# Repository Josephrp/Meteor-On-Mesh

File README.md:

# Meshtonic

**Meshtonic H4M Companion v2** is a custom carrier board and firmware stack for a [Seeed XIAO ESP32-S3 Plus](https://www.seeedstudio.com/Seeed-Studio-XIAO-ESP32S3-Plus-p-6361.html) that docks to a **HackRF + PortaPack H4M (Mayhem)** and can also run as a **standalone Meshtastic** mesh node.

**Repository:** [github.com/Josephrp/meshtonic](https://github.com/Josephrp/meshtonic) (formerly `Meteor-On-Mesh`)

| Mode | Role |
|------|------|
| **Docked (Mayhem MDK)** | ESP32 is an I2C slave at `0x51` on the PortaPack MDK connector. Exposes GPS, sensors, web UI, and 1–4 LoRa radios to Mayhem; runs the on-device LoRa decoder EPApp. |
| **Standalone (Meshtastic)** | Flash the Meshtastic image instead. Board becomes a LoRa mesh node with GPS, TFT, and muxed sensors. |

The two ESP32 firmwares are **mutually exclusive** — flash one or the other depending on whether you are using the board docked or as a mesh node.

---

## Hardware overview

| Block | Parts |
|-------|--------|
| **MCU** | Seeed XIAO ESP32-S3 Plus (ESP32-S3, 16 MB flash, OPI PSRAM) |
| **LoRa** | Up to **4×** [Wio-SX1262](https://www.seeedstudio.com/) shields — shared SPI, per-radio CS on native GPIO, BUSY/DIO1/RST via **MCP23017** `@ 0x20` |
| **Sensors** | **TCA9548A** `@ 0x70` mux: BMM150, BMP280, SHT3x, BMI160; **AS5600** on the main I2C bus |
| **GPS** | NEO-6M (UART1) |
| **Display / storage** | ILI9341 240×320 SPI TFT, microSD |
| **Host link** | PortaPack H4M / MDK-compatible connector (I2C slave + power) |
| **Power** | USB / solar → **CN3170** LiPo charge → **TPS63020** 3.3 V buck-boost |

Canonical pin map (silicon GPIO numbers for the XIAO Plus — `Dn ≠ GPIOn` above D5):

- Shared SPI: MOSI / MISO / SCK = GPIO 38 / 39 / 40  
- I2C: SDA / SCL = GPIO 5 / 6  
- WIO1–4 CS: GPIO 3 / 4 / 10 / 13  
- MCP INTA: GPIO 44 · WIO1 DIO1: GPIO 12  
- Full table: [`firmwares/pin_mapping.cpp`](firmwares/pin_mapping.cpp) and the variant [`PIN_AUDIT.md`](firmwares/meshtastic/variants/esp32s3/diy/meshtonic_h4m_wio1/PIN_AUDIT.md)

<p align="center">
  
  <br />

</p>

Architecture notes for the docked LoRa path (MCP ISR → radio manager → decoder → web / PortaPack) live in [`static/diagrams.md`](static/diagrams.md).

### Enclosure

3D-printable case STLs (65 × 140 mm footprint):

- [`case/enclosure_base_65x140x32.stl`](case/enclosure_base_65x140x32.stl)
- [`case/enclosure_lid_65x140.stl`](case/enclosure_lid_65x140.stl)

---

## Software stack

| Tree | Upstream | Meshtonic role |
|------|----------|----------------|
| [`firmwares/meshtastic/`](firmwares/meshtastic/) | [Meshtastic firmware](https://github.com/meshtastic/firmware) (GPL-3.0) | Custom board env `meshtonic-h4m-wio1` — WIO1-first standalone mesh |
| [`firmwares/mayhem-mdk/`](firmwares/mayhem-mdk/) | [ESP32-Portapack / Mayhem MDK](https://github.com/htotoo/ESP32-Portapack) (HTL) | Docked companion: `HW_VARIANT_MESHTONIC_H4M`, MCP + TCA drivers, multi-slot SX1262 manager, LoRa decoder EPApp, optional host LWD bridge |
| [`firmwares/mayhem-firmware/`](firmwares/mayhem-firmware/) | [PortaPack Mayhem](https://github.com/portapack-mayhem/mayhem-firmware) (GPL-3.0) | Vendored Mayhem tree + PortaPack UI app under `firmware/standalone/meshtonic_lora/` |

Shared first-party pin constants: [`firmwares/pin_mapping.cpp`](firmwares/pin_mapping.cpp).

### Docked LoRa decoder (MDK)

When Mayhem MDK is flashed with the Meshtonic H4M profile:

1. ESP32 auto-runs the LoRa Decoder EPApp.
2. Up to four Wio-SX1262 modules listen in parallel (narrowband).
3. Optional HackRF wideband path: PortaPack sends short IQ bursts over I2C (`0xA012`); ESP DSP + decode run on-device.
4. Status and packets paint on the PortaPack LCD (Apps over I2C) and/or the ESP web UI.

Protocol and backend IDs: [`firmwares/mayhem-mdk/docs/PORTAPACK_LORADEC.md`](firmwares/mayhem-mdk/docs/PORTAPACK_LORADEC.md).

```mermaid
flowchart TD
  Board["Meshtonic H4M (1-4 Wio SX1262)"] -->|MCP23017 + shared SPI| Radios["LoraRadio slots"]
  Radios --> EPApp["EPAppLoraDecoder"]
  EPApp --> Decode["Decode layer"]
  Decode --> Packets["LoraPacket"]
  Packets --> Web["Web / WS"]
  Packets --> PP["PortaPack I2C @ 0x51"]
  HostLWD["Host LWD optional"] -.-> Packets
```

---

## Repository map

```
meshtonic/
├── pcb/                 # KiCad project meshtonic_h4m_v2 (schematics, PCB, BOM, DFM)
├── firmwares/
│   ├── meshtastic/      # Meshtastic + meshtonic_h4m_wio1 variant
│   ├── mayhem-mdk/      # ESP32 Mayhem MDK + Meshtonic H4M profile
│   ├── mayhem-firmware/ # PortaPack Mayhem (+ meshtonic_lora PP app)
│   └── pin_mapping.cpp  # Canonical H4M v2 GPIO / MCP map
├── case/                # Enclosure STLs
├── static/              # Photos, pinout / architecture diagrams, demos
└── README.md
```

Local-only (gitignored) folders such as `refs/` and `backups/` may hold design plans and PCB snapshots on a developer machine; they are not part of the tracked tree.

---

## Getting started

### Prerequisites

| Firmware | Toolchain |
|----------|-----------|
| Meshtastic | [PlatformIO](https://platformio.org/) (CLI or IDE) |
| Mayhem MDK | [ESP-IDF](https://docs.espressif.com/projects/esp-idf/en/latest/esp32s3/) targeting `esp32s3`, or the Docker builders under `firmwares/mayhem-mdk/docker/` |
| PortaPack app | Mayhem firmware build environment (see upstream Mayhem docs) |

Hardware bring-up checklist (I2C scan + radio):

- MCP23017 `@ 0x20`, TCA9548A `@ 0x70`, AS5600 `@ 0x36`
- SX1262 init on populated WIO slot(s)
- GPS NMEA on UART1
- ILI9341 bring-up (standalone Meshtastic)
- LoRa TX/RX with a second Meshtastic node (standalone)

### Flash Meshtastic (standalone)

```bash
cd firmwares/meshtastic
pio run -e meshtonic-h4m-wio1
pio run -e meshtonic-h4m-wio1 -t upload
pio device monitor -b 115200
```

- Board definition: [`boards/meshtonic_h4m_wio1.json`](firmwares/meshtastic/boards/meshtonic_h4m_wio1.json)
- Variant docs: [`variants/esp32s3/diy/meshtonic_h4m_wio1/`](firmwares/meshtastic/variants/esp32s3/diy/meshtonic_h4m_wio1/)
- Upload uses esptool @ 921600 with 1200 bps touch / wait-for-port (16 MB flash)
- Current Meshtastic port is **WIO1-first** (one radio). Multi-radio listening is implemented on the MDK side.

### Flash Mayhem MDK (docked companion)

```bash
cd firmwares/mayhem-mdk/Source
idf.py set-target esp32s3
# Select Meshtonic H4M pins: HW_VARIANT_MESHTONIC_H4M in code,
# and/or choose "Meshtonic H4M" in the web pin-config UI after first boot
idf.py build
idf.py -p <PORT> flash monitor
```

Docker alternative:

```bash
cd firmwares/mayhem-mdk/docker
# see build.ps1 / build-in-container.sh / docker-compose.yml
```

Pin preset for Meshtonic H4M: GPS RX = GPIO 7, shared I2C master+slave on GPIO 5/6 (`HW_VARIANT_MESHTONIC_H4M` in [`pinconfig.h`](firmwares/mayhem-mdk/Source/main/pinconfig.h)).

Optional host-side LoRa wideband decoder / bridge tooling: [`firmwares/mayhem-mdk/lora-wideband-decoder/`](firmwares/mayhem-mdk/lora-wideband-decoder/).

### PortaPack “Meshtonic LoRa” app

PortaPack-side UI that talks to the ESP over Apps-over-I2C lives in:

- [`firmwares/mayhem-firmware/firmware/standalone/meshtonic_lora/`](firmwares/mayhem-firmware/firmware/standalone/meshtonic_lora/)
- Reference / example: [`firmwares/mayhem-mdk/Source/extapps/meshtonic_lora_ui_example.cpp`](firmwares/mayhem-mdk/Source/extapps/meshtonic_lora_ui_example.cpp)

Build and install that app with your usual Mayhem standalone-app workflow, then launch it from the PortaPack App Manager (or rely on Meshtonic H4M auto-start of the ESP decoder).

---

## PCB and manufacturing

KiCad 8 project: **`pcb/meshtonic_h4m_v2`**

| Sheet | Contents |
|-------|----------|
| `meshtonic_h4m_v2.kicad_sch` | Root |
| `Power` | CN3170 charge, TPS63020 3.3 V, battery / solar |
| `Xiao_Core` | XIAO ESP32-S3 Plus |
| `LoRa` | WIO1–4 sockets, MCP23017 radio GPIO |
| `Sensors` | TCA9548A + environmental / IMU / mag |
| `Periferals` | TFT, microSD, GPS, Grove, misc |
| `H4M_Connector` / `MDK_Interface` | PortaPack dock |
| `Breakout_GPIO` | Expansion |

Also: `meshtonic_i2c-hub.kicad_*` for the I2C hub side project.

### BOM / fab

| Artifact | Purpose |
|----------|---------|
| [`pcb/meshtonic_h4m_v2.csv`](pcb/meshtonic_h4m_v2.csv) | Seeed Fusion–oriented PCBA BOM |
| [`pcb/meshtonic_h4m_v2_excluded_from_pcba.csv`](pcb/meshtonic_h4m_v2_excluded_from_pcba.csv) | Hand-fit / DNP (WIO sockets, display, test points, …) |
| [`pcb/_gen_seeed_bom.py`](pcb/_gen_seeed_bom.py) | Regenerates the Seeed BOM + exclusion list |
| [`pcb/dfm/`](pcb/dfm/) | Gerbers, drills, fab zip |

**Hand-fit after PCBA:** Wio-SX1262 modules (and their hybrid SMD+TH landings), display module, and any DNP connectors listed in the exclusion CSV.

Regenerate the Fusion BOM:

```bash
python pcb/_gen_seeed_bom.py
```

---

## Status

This is an active hardware + firmware bring-up project.

- PCB: Meshtonic H4M Companion **v2** (iterating layout / DFM)
- Meshtastic: custom `meshtonic-h4m-wio1` env — single-radio focus
- Mayhem MDK: Meshtonic H4M board profile, multi-radio LoRa decoder path in development
- PortaPack UI app and host LWD bridge: present; expect ongoing protocol/UI work

Demo media: [`static/`](static/) (photos + short videos).

---

## Licenses

This is a **multi-license** monorepo. The root [`LICENSE`](LICENSE) is the index; full texts live under [`LICENSES/`](LICENSES/).

| Component | License |
|-----------|---------|
| `pcb/`, `case/`, `firmwares/pin_mapping.cpp` | [CERN-OHL-P-2.0](LICENSES/CERN-OHL-P-2.0.txt) |
| `README.md`, `static/` | [CC-BY-4.0](LICENSES/CC-BY-4.0.txt) |
| `firmwares/meshtastic/` | [GPL-3.0](firmwares/meshtastic/LICENSE) |
| `firmwares/mayhem-firmware/` | GPL-3.0 (see tree) |
| `firmwares/mayhem-mdk/` | Custom **HTL** — attribution, contribute improvements back, **no commercial use** ([`LICENSE`](firmwares/mayhem-mdk/LICENSE)) |
| `firmwares/mayhem-mdk/lora-wideband-decoder/` | See that subtree’s `LICENSE` |
| `pcb/libs/` | Upstream library licenses (unchanged) |

Meshtonic board support added inside a firmware tree follows that tree’s license unless a file says otherwise. Upstream copyrights remain with their respective authors.

---

## Links

- [This repository](https://github.com/Josephrp/meshtonic)
- [Meshtastic](https://meshtastic.org) · [firmware](https://github.com/meshtastic/firmware)
- [PortaPack Mayhem](https://github.com/portapack-mayhem/mayhem-firmware)
- [ESP32-Portapack / Mayhem MDK](https://github.com/htotoo/ESP32-Portapack) · [wiki](https://github.com/htotoo/ESP32-Portapack/wiki)
- [Seeed XIAO ESP32-S3 Plus](https://www.seeedstudio.com/Seeed-Studio-XIAO-ESP32S3-Plus-p-6361.html)
- In-repo diagrams: [`static/diagrams.md`](static/diagrams.md) · LoRa over I2C: [`docs/PORTAPACK_LORADEC.md`](firmwares/mayhem-mdk/docs/PORTAPACK_LORADEC.md)

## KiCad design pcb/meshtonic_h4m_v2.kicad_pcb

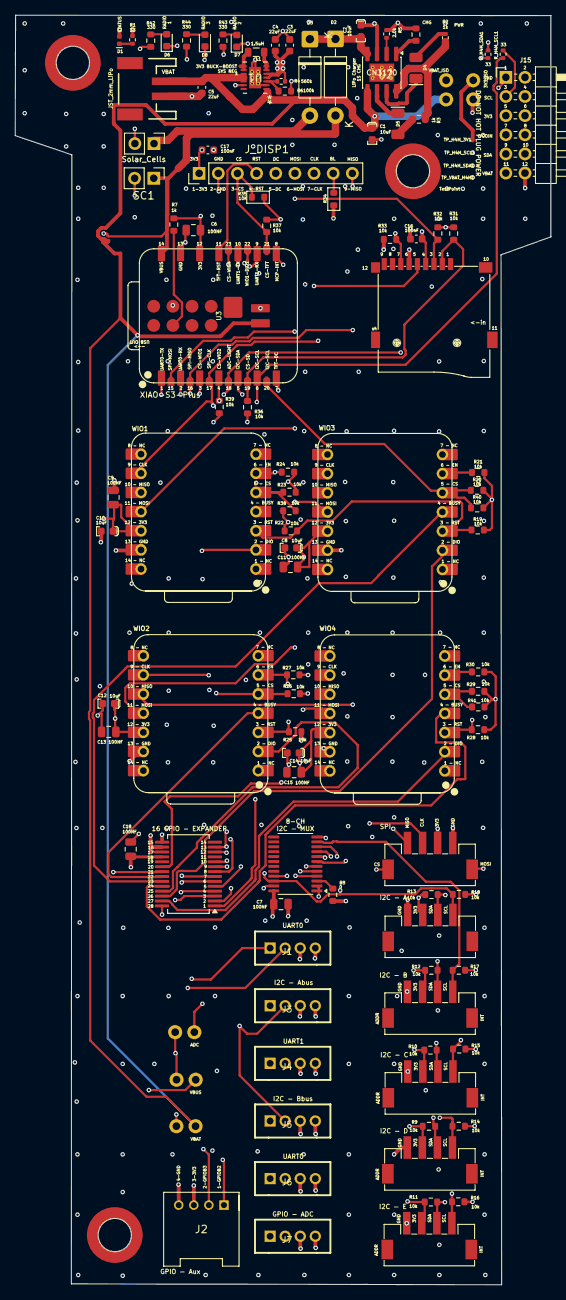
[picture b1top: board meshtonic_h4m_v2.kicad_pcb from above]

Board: 6 copper layers, 71.1 x 168.4 mm, 115 parts (0 on the bottom side), 70 nets.

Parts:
C1, C2, C8, C10, C12, C14: 10uF; C_0603_1608Metric_Polar
C3, C4, C5: 22uF; C_0603_1608Metric
C6, C7, C9, C11, C13, C15, C18: CERAMIC-100NF-50V-10%-X7R_0805_; C_0805_2012Metric
C16, C17: 100nF; C_0603_1608Metric
D1: Red; LED_0402_1005Metric_Red
D2, D3: 1N5819; D_DO-41_SOD81_P10.16mm_Horizontal
D4, D5: Green; LED_1206_3216Metric_Green
D6, D7, D8: LED-SMD-RED-DIFFUSED_0603_; LED_0603_1608Metric
J1, J3, J4, J5, J6, J7: GROVE-CONNECTOR-DIP_4P-2.0_; GROVE-HW4-2.0
J2: GROVE-CONNECTOR-DIP-90D_4P-2.0_; GROVE-HW4-2.0-90D
J8: GROVE-CONNECTOR-SMD_4+2P-2.0_; GROVE-HW4-SMD-2.0
J9, J10, J11: Conn_01x02; 1x02_P2.54mm
J12: JST_2mm_LiPo; JST_1x02_P2.0mm_Horizontal_SMD
J13: Screw_Terminal_01x02; PinHeader_1x02_P2.54mm_Vertical
J14: Micro_SD_Card_passive_clk; MICRO-SD9+4P-SMD-16.1X14.5X1.85MM
J15: H4M_2x6_MDK; PinHeader_2x06_P2.54mm_Horizontal
JP_H4M_3V1: 3V3_ISO; 1x02_P2.54mm
JP_VBAT_H4M1: VBAT_ISO; 1x02_P2.54mm
J_AS1: AS5600_LANDING; GROVE-HW4-SMD-2.0
J_BMI1: BMI160_LANDING; GROVE-HW4-SMD-2.0
J_BMM1: BMM150_LANDING; GROVE-HW4-SMD-2.0
J_BMP1: BMP280_LANDING; GROVE-HW4-SMD-2.0
J_DISP1: DISP_SPI_9P; PinHeader_1x09_P2.54mm_Vertical
J_SHT1: SHT31_LANDING; GROVE-HW4-SMD-2.0
J_WIO1, J_WIO2, J_WIO3, J_WIO4: WioSX1262_Shield_Socket; XIAO-ESP32-S3-DIP
L1: 1.5uH; 0805
R1: 33; R_0402_1005Metric
R2: 1k; R_0402_1005Metric
R3, R7: 1k; R_0603_1608Metric
R4: 560k; R_0402_1005Metric
R5: 2.0k; R_0402_1005Metric
R6: 100k; R_0603_1608Metric
R8, R34: 0; R_0603_1608Metric
R9, R10, R11, R12, R13, R14, R15, R16, R17, R18, R19, R20, R21, R22, R23, R24, R25, R26, R27, R28, R29, R30, R31, R32, R33, R35, R36, R37, R38, R39, R40, R41, R45: 10k; R_0603_1608Metric
R42, R43, R44: 330; R_0603_1608Metric
R_H4M_SCL1, R_H4M_SDA1: 33; R_0402_1005Metric
SC1: Solar_Cells; PinHeader_1x02_P2.54mm_Vertical
ST1, ST2, ST3: Standoff; Standoff_Reflow-M3.0
TP1: TestPoint; TestPoint-0.5mm
TP_H4M_3V1, TP_H4M_SCL1, TP_H4M_SDA1: 0.5mm; TestPoint-0.5mm
TP_VBAT_H4M1: 0.5mm; TestPoint-0.5mm
U1: TPS63020DSJR; DSJ14_2P85X1P58
U2: CN3170; SOIC-8-1EP_3.9x4.9mm_P1.27mm_EP2.41x3.3mm_ThermalVias
U3: XIAO-S3-Plus; XIAO-ESP32-S3-Plus-SMD
U4: TCA9548APWR; TSSOP-24_4.4x7.8mm_P0.65mm
U5: MCP23017x-x-SS; SSOP-28_5.3x10.2mm_P0.65mm

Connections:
3V3: C3.1, C4.1, C6.2, C7.1, C8.1, C9.1, C10.1, C11.1, C12.1, C13.1, C14.1, C15.1, C16.1, C17.2, C18.2, D1.2 (A), D6.1 (+), D7.1 (+), D8.1 (+), J1.3, J2.3, J3.3, J4.3, J5.3, J6.3, J7.3, J8.2, J14.4 (VDD), JP_H4M_3V1.2, J_AS1.3, J_BMI1.3, J_BMM1.3, J_BMP1.3, J_DISP1.1 (VCC), J_SHT1.3, J_WIO1.12, J_WIO2.12, J_WIO3.12, J_WIO4.12, R4.1, R7.2, R8.1, R9.1, R10.1, R11.1, R12.1, R13.1, R14.1, R15.1, R16.1, R17.1, R18.1, R19.2, R20.2, R21.2, R22.2, R23.2, R24.2, R25.2, R26.2, R27.2, R28.2, R29.2, R30.2, R31.2, R32.2, R33.2, R34.2, R35.2, R36.2, R37.2, R38.2, R39.2, R40.2, R41.2, U1.4 (VOUT), U1.5 (VOUT), U3.12 (3V3_OUT), U4.24 (VCC), U5.9 (V_{DD}), U5.18 (~RESET)
/Periferals/LED WIO 1: R42.1, U5.6 (GPB5)
/Periferals/LED WIO 2: R43.1, U5.7 (GPB6)
/Periferals/LED WIO 3: R44.1, U5.8 (GPB7)
/Power/VIN_CHG: C2.2, D2.1 (K), D3.1 (K), U2.4 (VIN)
ADC_LIGHT: J7.2, J11.1, TP1.1 (1_1), U3.18 (D14)
CS_GROVE: J8.6, U5.2 (GPB1)
CS_SD: J14.2 (DAT3/CD), R31.1, R36.1, U3.19 (D15)
CS_TFT: J_DISP1.3 (CS), R35.1, R37.1, U3.21 (D19)
CS_WIO1: J_WIO1.5, R23.1, R38.1, U3.3 (D2)
CS_WIO2: J_WIO2.5, R26.1, R39.1, U3.4 (D3)
CS_WIO3: J_WIO3.5, R20.1, R40.1, U3.20 (D16)
CS_WIO4: J_WIO4.5, R29.1, R41.1, U3.23 (D17)
GND: C1.2, C2.1, C3.2, C4.2, C5.1, C6.1, C7.2, C8.2, C9.2, C10.2, C11.2, C12.2, C13.2, C14.2, C15.2, C16.2, C17.1, C18.1, J1.4, J2.4, J3.4, J4.4, J5.4, J6.4, J7.4, J8.1, J9.2, J10.2, J11.2, J12.1 (-), J13.2, J14.6 (VSS), J15.1, J15.12, J_AS1.4, J_BMI1.4, J_BMM1.4, J_BMP1.4, J_DISP1.2 (GND), J_SHT1.4, J_WIO1.13, J_WIO2.13, J_WIO3.13, J_WIO4.13, R1.2, R5.1, R6.1, R45.2, SC1.2 (-), U1.2 (GND), U1.13 (PS/SYNC), U1.15 (EPAD), U2.3 (GND), U2.9 (GND), U3.13 (GND), U3.27 (GND), U3.33 (GND), U4.1 (A0), U4.2 (A1), U4.12 (GND), U4.21 (A2), U5.10 (V_{SS}), U5.15 (A0), U5.16 (A1), U5.17 (A2)
H4M_3V3: J15.5, J15.8, JP_H4M_3V1.1, TP_H4M_3V1.1 (1_1)
H4M_SCL: J15.3, J15.10, R_H4M_SCL1.1, TP_H4M_SCL1.1 (1_1)
H4M_SDA: J15.4, J15.9, R_H4M_SDA1.1, TP_H4M_SDA1.1 (1_1)
I2C_SCL: J3.1, J5.1, J_AS1.1, R18.2, R_H4M_SCL1.2, U3.6 (D5), U4.22 (SCL), U5.12 (SCK)
I2C_SDA: J3.2, J5.2, J_AS1.2, R13.2, R_H4M_SDA1.2, U3.5 (D4), U4.23 (SDA), U5.13 (SDA)
LORA_RST: J_WIO1.3, J_WIO2.3, J_WIO3.3, J_WIO4.3, R19.1, R22.1, R25.1, R28.1, U5.5 (GPB4)
MCP_GPA7: J7.1, U5.28 (GPA7)
MCP_GPB2: J2.1, U5.3 (GPB2)
MCP_GPB3: J2.2, U5.4 (GPB3)
MCP_INT: U3.8 (D7), U5.20 (INTA)
unnamed: D1.1 (K), R1.1
unnamed: D4.2 (A), R2.2
unnamed: D4.1 (K), U2.7 (~CHRG)
unnamed: D5.2 (A), R3.2
unnamed: D5.1 (K), U2.6 (~DONE)
unnamed: D6.2 (-), R42.2
unnamed: D7.2 (-), R43.2
unnamed: D8.2 (-), R44.2
unnamed: L1.1, U1.6 (L2), U1.7 (L2)
unnamed: L1.2, U1.8 (L1), U1.9 (L1)
unnamed: R4.2, R6.2, U1.3 (FB)
unnamed: R5.2, U2.2 (ISET)
unnamed: R45.1, U2.1 (TEMP)
unnamed: R7.1, U3.26 (EN)
unnamed: R8.2, U4.3 (~RESET)
SENS0_SCL: J_BMM1.1, R14.2, U4.5 (SC0)
SENS0_SDA: J_BMM1.2, R9.2, U4.4 (SD0)
SENS1_SCL: J_BMP1.1, R15.2, U4.7 (SC1)
SENS1_SDA: J_BMP1.2, R10.2, U4.6 (SD1)
SENS2_SCL: J_SHT1.1, R16.2, U4.9 (SC2)
SENS2_SDA: J_SHT1.2, R11.2, U4.8 (SD2)
SENS3_SCL: J_BMI1.1, R17.2, U4.11 (SC3)
SENS3_SDA: J_BMI1.2, R12.2, U4.10 (SD3)
SPI_CLK: J8.3, J14.5 (CLK), J_DISP1.7 (SCK), J_WIO1.9, J_WIO2.9, J_WIO3.9, J_WIO4.9, U3.17 (D13)
SPI_MISO: J8.4, J14.7 (DAT0), J_DISP1.9 (MISO), J_WIO1.10, J_WIO2.10, J_WIO3.10, J_WIO4.10, R33.1, U3.16 (D12)
SPI_MOSI: J8.5, J14.3 (CMD), J_DISP1.6 (MOSI), J_WIO1.11, J_WIO2.11, J_WIO3.11, J_WIO4.11, R32.1, U3.15 (D11)
TFT_BL: J_DISP1.8 (LED), R34.1
TFT_DC: J_DISP1.5 (D/C), U3.7 (D6)
TFT_RST: J_DISP1.4 (RESET), U3.11 (D10)
UART0_RX: J1.1, J6.1, U3.2 (D1)
UART0_TX: J1.2, J6.2, U3.1 (D0)
UART1_RX: J4.1, U3.9 (D8)
UART1_TX: J4.2, U3.10 (D9)
VBAT: C1.1, C5.2, J9.1, J12.2 (+), JP_VBAT_H4M1.2, R2.1, R3.1, U1.1 (VINA), U1.10 (VIN), U1.11 (VIN), U1.12 (EN), U2.5 (BAT), U2.8 (FB), U3.32 (VBAT)
VBAT_H4M: J15.2, J15.11, JP_VBAT_H4M1.1, TP_VBAT_H4M1.1 (1_1)
VBUS: D2.2 (A), D3.2 (A), J10.1, J13.1, SC1.1 (+), U3.14 (VBUS)
VCOIN_H4M: J15.6, J15.7
WIO1_BUSY: J_WIO1.4, U5.21 (GPA0)
WIO1_DIO1: J_WIO1.2, U3.22 (D18)
WIO2_BUSY: J_WIO2.4, U5.22 (GPA1)
WIO2_DIO1: J_WIO2.2, U5.25 (GPA4)
WIO3_BUSY: J_WIO3.4, U5.23 (GPA2)
WIO3_DIO1: J_WIO3.2, U5.26 (GPA5)
WIO4_BUSY: J_WIO4.4, U5.24 (GPA3)
WIO4_DIO1: J_WIO4.2, U5.27 (GPA6)
WIO_RF_SW_EN: J_WIO1.6, J_WIO2.6, J_WIO3.6, J_WIO4.6, R21.1, R24.1, R27.1, R30.1, U5.1 (GPB0)

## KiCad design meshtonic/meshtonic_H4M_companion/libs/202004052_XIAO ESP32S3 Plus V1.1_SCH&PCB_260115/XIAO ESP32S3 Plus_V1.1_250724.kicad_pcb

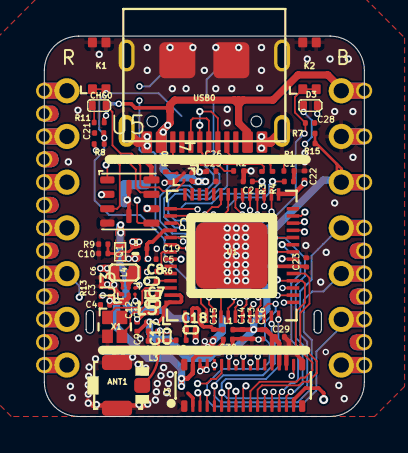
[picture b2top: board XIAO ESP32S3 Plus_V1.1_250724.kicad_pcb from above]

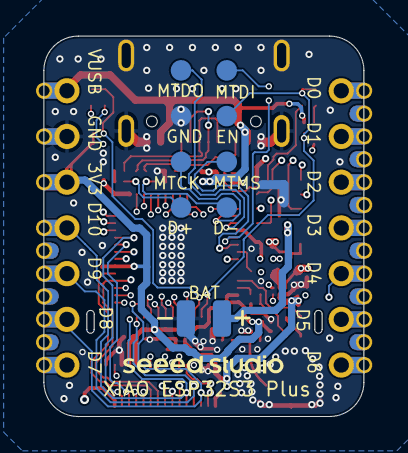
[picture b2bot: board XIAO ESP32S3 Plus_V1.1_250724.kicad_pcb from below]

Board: 6 copper layers, 17.8 x 21.1 mm, 70 parts (10 on the bottom side), 62 nets.

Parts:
ANT1: U.FL-R-SMT-1; U-FL3P-SMD-2.6X2.6X1.0MM
BAT0: VBAT; TP-80X40MIL
C1, C2, C20: DNP; C0201
C3, C9, C13, C16: 2.2uF; C0201
C4, C5, C6: 4.7uF; C0201
C7, C8: 12pF; C0201
C10, C21, C25, C26: 1uF; C0201
C11, C14, C15, C19, C22, C23, C29, C30: 100nF; C0201
C12: 10nF; C0201
C17: 1.2pF; C0201
C18: 1.8pF; C0201
C28: 10pF; C0201
CHG0: RED; LED-0402
D2: LMBR4010BST5G; DFN1006-2L
D3: Yellow; LED-0402
GND0: GND; TP-80X40MIL
J3: 30pin; BTB30-0.4-7.52X2.97X1.14
K1, K2: SKTAAAE010/311021459; SW4-SMD-2.8-2.6X1.6X0.53MM
L1: 2nH; L0201
L2: 3.3nH; L0201
L3: DNP; L0201
L4: 470nH; L0603
L5: 24nH; L0201
Q1: PMOS_1.00.60.35MM; PMOS_1.0*0.6*0.35MM
R1, R2: 5.1K; R0201
R3, R4: 22R; R0201
R6: 499R; R0201
R7, R8, R11: 10K; R0201
R9: 100K; C0201
R10: 220K; R0201
R13: 249K; R0201
R15: 1.5K; R0201
TP1, TP2, TP3, TP4, TP5, TP6, TP7, TP8: TEST-POINT'4545'; TP-D45MIL
U1: MCU-ESP32-S3; QFN56G-0.4-7X7MM
U2: XIAO-HALF-HOLE-23P; MOUDLE23P-XIAO-HALF-HOLE
U3: SGM6029CYG/TR; BGA6-0.35-0.85X1.2X0.4MM
U4: SGM40567-4.2XG/TR; WLCSP-0.4-0.92X1.16X0.4MM
U5: PY25Q128HA-DFH-IR; USON8-0.8-3X3X0.55MM
USB0: UBF31-0171; USB2.0-TYPE-C
X1: 40MHz; X4-SMD-1.6X1.2X0.35MM

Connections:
/D0/A0: U1.6 (GPIO1), U2.1 (GPIO1_D0/A0)
/D1/A1: U1.7 (GPIO2), U2.2 (GPIO2_D1/A1)
/D2/A2: J3.2, U1.8 (GPIO3), U2.3 (GPIO3_D2/A2)
/D3/A3: U1.9 (GPIO4), U2.4 (GPIO4_D3/A3)
/D4/A4/I2C_SDA: U1.10 (GPIO5), U2.5 (GPIO5_D4/A4/I2C_SDA)
/D5/A5/I2C_SCL: U1.11 (GPIO6), U2.6 (GPIO6_D5/A5/I2C_SCL)
/D6/TX: R6.2, U2.7 (U0TXD_D6/TX)
/D7/RX: U1.50 (U0RXD), U2.8 (U0RXD_D7/RX)
/D8/A8/SCK: J3.3, U1.12 (GPIO7), U2.9 (GPIO7_D8/A8/SCK)
/D9/A9/MISO: J3.4, U1.13 (GPIO8), U2.10 (GPIO8_D9/A9/MISO)
/D10/A10/MOSI: J3.5, U1.14 (GPIO9), U2.11 (GPIO9_D10/A10/MOSI)
/EN: C21.2, K1.1 (A0), K1.3 (A1), R8.1, TP6.T, U1.4 (CHIP_PU)
/ESP_USB_D+: C1.2, R4.2, TP8.T, U1.26 (GPIO20)
/ESP_USB_D-: C2.2, R3.2, TP7.T, U1.25 (GPIO19)
/GPIO0: C28.2, K2.1 (A0), K2.3 (A1), R7.1, U1.5 (GPIO0)
/IO10/XMCLK/ADC_BAT: J3.6, U1.15 (GPIO10), U2.20 (GPIO10_XMCLK/ADC_BAT)
/IO11/DVP_Y8/SPI_MOSI1: J3.7, U1.16 (GPIO11), U2.21 (GPIO11_DVP_Y8/SPI_MOSI1)
/IO12/DVP_Y7/SPI_MISO1: J3.8, U1.17 (GPIO12), U2.22 (GPIO12_DVP_Y7/SPI_MISO1)
/IO13/DVP_PCLK/SPI_SCK1: J3.9, U1.18 (GPIO13), U2.23 (GPIO13_DVP_PCLK/SPI_SCK1)
/IO14/DVP_Y6: J3.10, U1.19 (GPIO14)
/IO15/DVP_Y2: J3.11, U1.21 (XTAL_32K_P)
/IO16/DVP_Y5: J3.12, U1.22 (XTAL_32K_N)
/IO17/DVP_Y3: J3.13, U1.23 (GPIO17)
/IO18/DVP_Y4: J3.14, U1.24 (GPIO18)
/IO21/USER_LED: D3.-, J3.16, U1.27 (GPIO21)
/IO38/DVP_VSYNC/I2S_SD: J3.23, U1.43 (GPIO38), U2.15 (GPIO38_DVP_VSYNC/I2S_SD)
/IO47/DVP_HREF: J3.22, U1.37 (SPICLK_P)
/IO48/DVP_Y9: J3.21, U1.36 (SPICLK_N)
/MTCK/IO39/CAM_SCL/I2S_SCK: J3.24, TP5.T, U1.44 (MTCK), U2.16 (GPIO39_CAM_SCL/I2S_SCK)
/MTDI/IO41/PDM_DATA/RX1: J3.26, TP3.T, U1.47 (MTDI), U2.18 (GPIO41_PDM_DATA/RX1)
/MTDO/IO40/CAM_SDA/I2S_WS: J3.25, TP4.T, U1.45 (MTDO), U2.17 (GPIO40_CAM_SDA/I2S_WS)
/MTMS/IO42/PDM_CLK/TX1: J3.27, TP2.T, U1.48 (MTMS), U2.19 (GPIO42_PDM_CLK/TX1)
/SPICLK: U1.33 (SPICLK), U5.6 (SCLK)
/SPICS0: U1.32 (SPICS0), U5.1 (CS#)
/SPID: U1.35 (SPID), U5.5 (SI)
/SPIHD: U1.30 (SPIHD), U5.7 (HOLD#/RESET#)
/SPIQ: U1.34 (SPIQ), U5.2 (SO)
/SPIWP: U1.31 (SPIWP), U5.3 (WP#)
/USB_D+: R4.1, USB0.A6 (A6/DP1), USB0.B6 (B6/DP2)
/USB_D-: R3.1, USB0.A7 (A7/DN1), USB0.B7 (B7/DN2)
/VBAT: BAT0.1 (T), C26.1, Q1.1 (D), U4.A1 (BAT)
/VBUS: C10.1, C25.1, D2.+, Q1.2 (G), R9.2, R11.1, U2.14 (VBUS), U4.A2 (VIN), USB0.A4_B9 (A4/B9/VBUS), USB0.B4_A9 (B4/A9/VBUS)
/VCC_3V3: C5.2, C6.2, C9.2, C11.2, C12.2, C13.2, C14.2, C16.2, C19.2, C23.1, C29.2, J3.18, J3.19, L1.1, L4.2, R7.2, R8.2, R15.2, U1.20 (VDD3P3_RTC), U1.46 (VDD3P3_CPU), U1.55 (VDDA@1), U1.56 (VDDA@2), U2.12 (VCC_3V3), U3.A2 (VOS)
/VDD_SPI: C22.2, U1.29 (VDD_SPI), U5.8 (VCC)
/VIN: C3.1, C4.1, C30.2, D2.-, J3.15, J3.30, Q1.3 (S), U3.B1 (VIN), U3.C2 (EN)
GND_POWER: ANT1.GND1, ANT1.GND2, C1.1, C2.1, C3.2, C4.2, C5.1, C6.1, C7.2, C8.1, C9.1, C10.2, C11.1, C12.1, C13.1, C14.1, C15.1, C16.1, C17.2, C18.2, C19.1, C20.1, C21.1, C22.1, C23.2, C25.2, C26.2, C28.1, C29.1, C30.1, GND0.1 (T), J3.17, J3.28, J3.29, J3.31, J3.33, J3.34, K1.2 (B0), K1.4 (B1), K2.2 (B0), K2.4 (B1), R1.1, R2.2, R9.1, R10.1, R13.1, TP1.T, U1.57 (GND), U2.13 (GND), U3.A1 (GND), U4.B1 (F), U4.C2 (GND), U5.4 (GND), U5.9 (GND), U5.10 (GND), USB0.A1_B12 (A1/B12/GND), USB0.B1_A12 (B1/A12/GND), USB0.S1, USB0.S2, USB0.S3, USB0.S4, USB0.S5 (S1), USB0.S6 (S2), X1.2 (GND), X1.4 (GND@1)
unnamed: ANT1.D, C17.1, L2.1, L3.2
unnamed: C20.2, L3.1
unnamed: CHG0.+, R11.2
unnamed: D3.+, R15.1
unnamed: C18.1, L2.2, U1.1 (LNA_IN)
unnamed: R6.1, U1.49 (U0TXD)
unnamed: C15.2, L1.2, U1.2 (VDD3P3@1), U1.3 (VDD3P3@2)
unnamed: C8.2, U1.53 (XTAL_N), X1.1 (X1)
unnamed: L5.1, U1.54 (XTAL_P)
unnamed: R13.2, U3.C1 (MODE)
unnamed: L4.1, U3.B2 (SW)
unnamed: R10.2, U4.C1 (IREF)
unnamed: CHG0.-, U4.B2 (NCHG)
unnamed: R1.2, USB0.A5 (A5/CC1)
unnamed: R2.1, USB0.B5 (B5/CC2)
unnamed: C7.1, L5.2, X1.3 (X2)

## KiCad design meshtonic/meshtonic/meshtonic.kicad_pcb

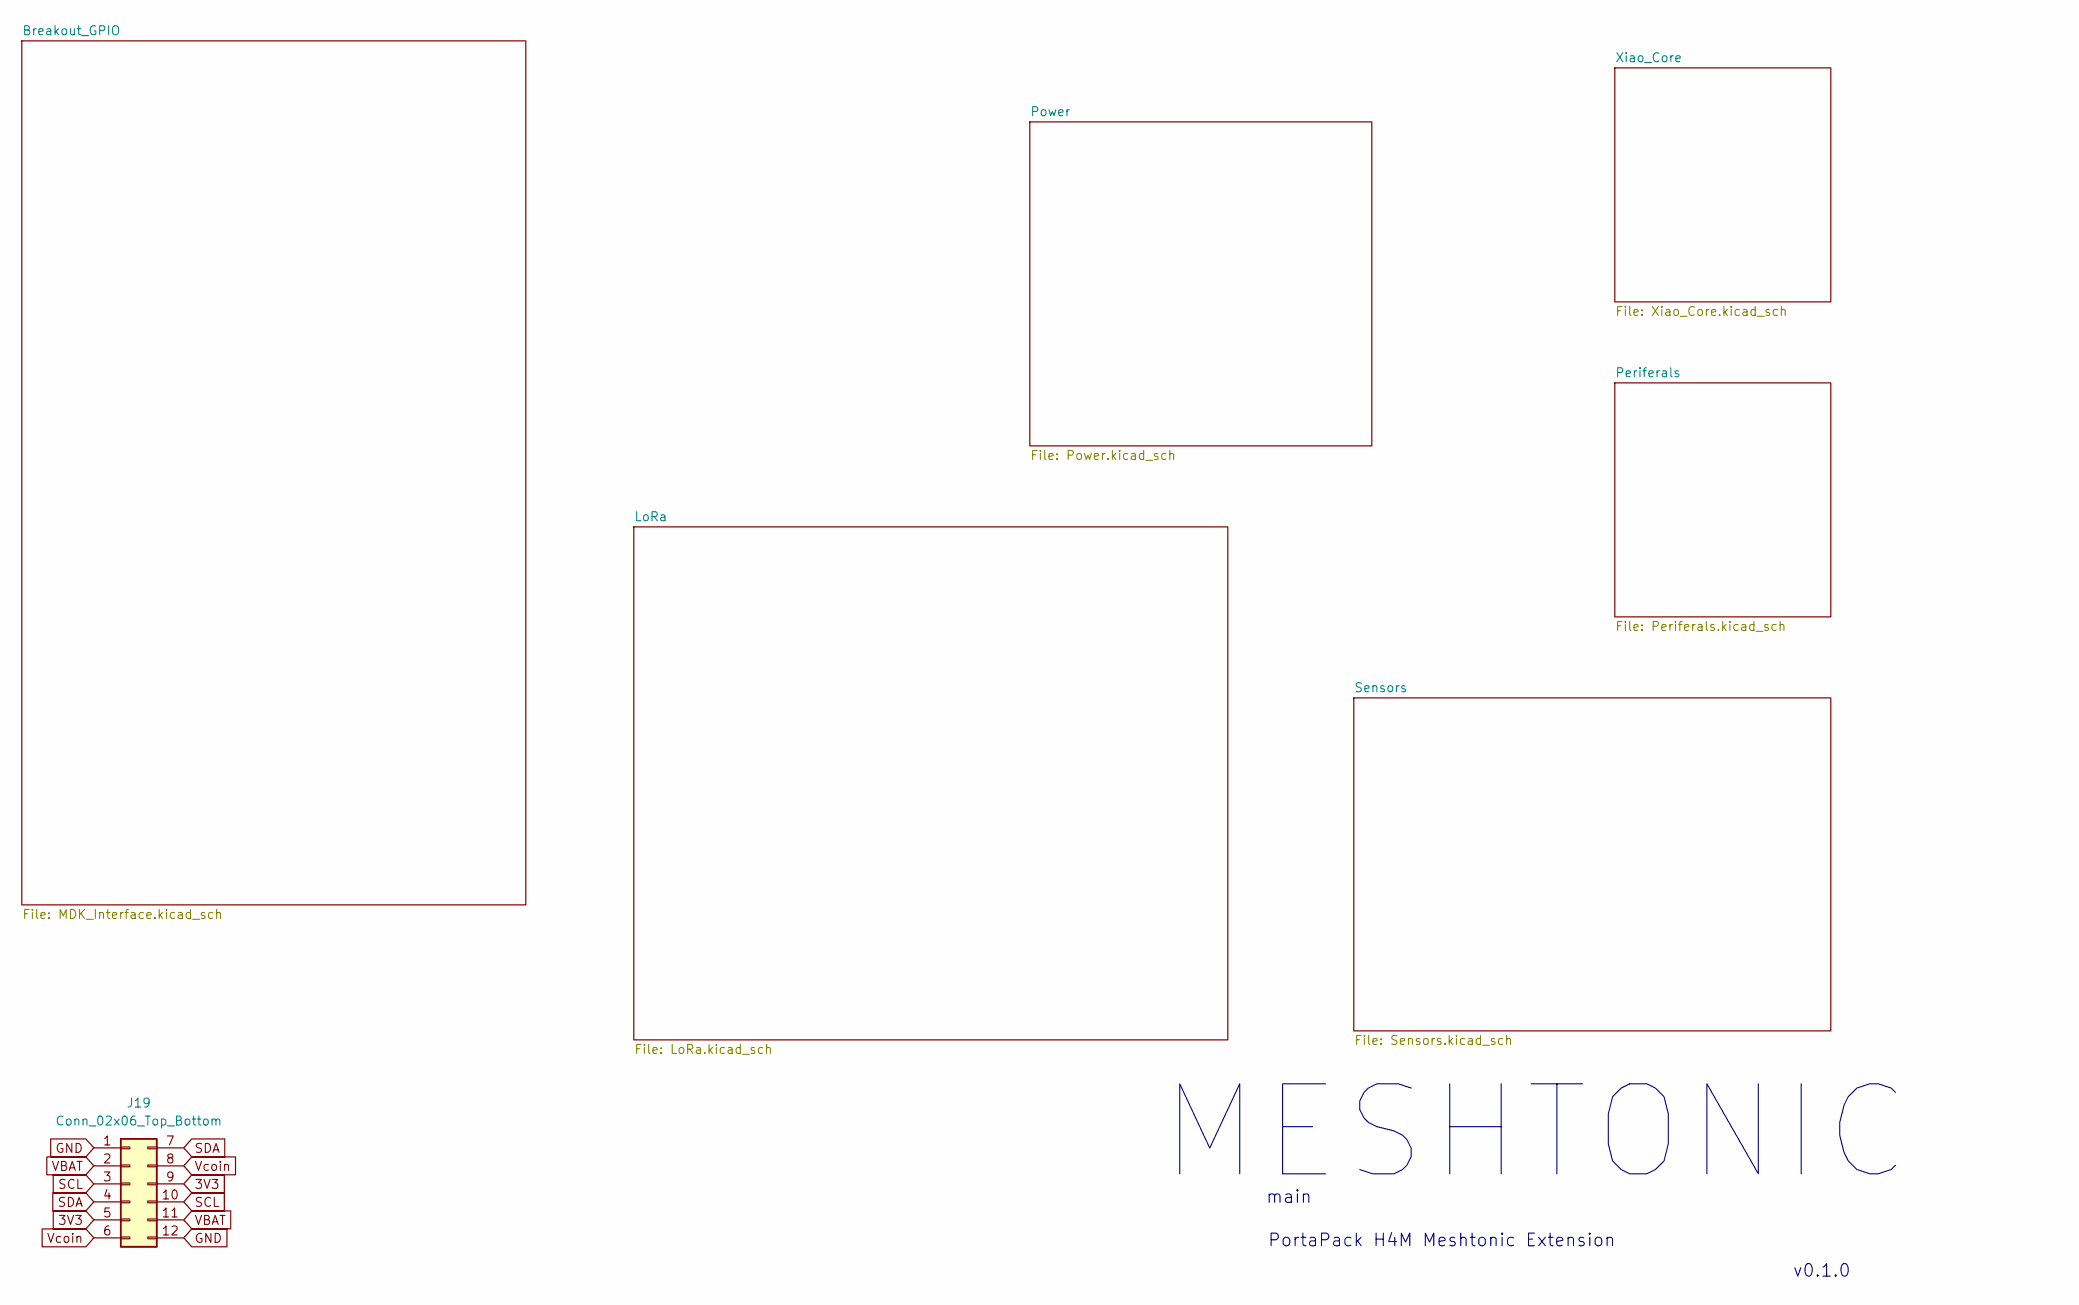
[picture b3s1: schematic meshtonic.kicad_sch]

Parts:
J19: Conn_02x06_Top_Bottom; PinHeader_2x06_P2.54mm_Horizontal

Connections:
3V3: J19.5, J19.9; also elsewhere on the board
GND: J19.1, J19.12; also elsewhere on the board
SCL: J19.3, J19.10; also elsewhere on the board
SDA: J19.4, J19.7; also elsewhere on the board
VBAT: J19.2, J19.11; also elsewhere on the board
Vcoin: J19.6, J19.8

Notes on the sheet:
PortaPack H4M Meshtonic Extension
MESHTONIC
v0.1.0
main

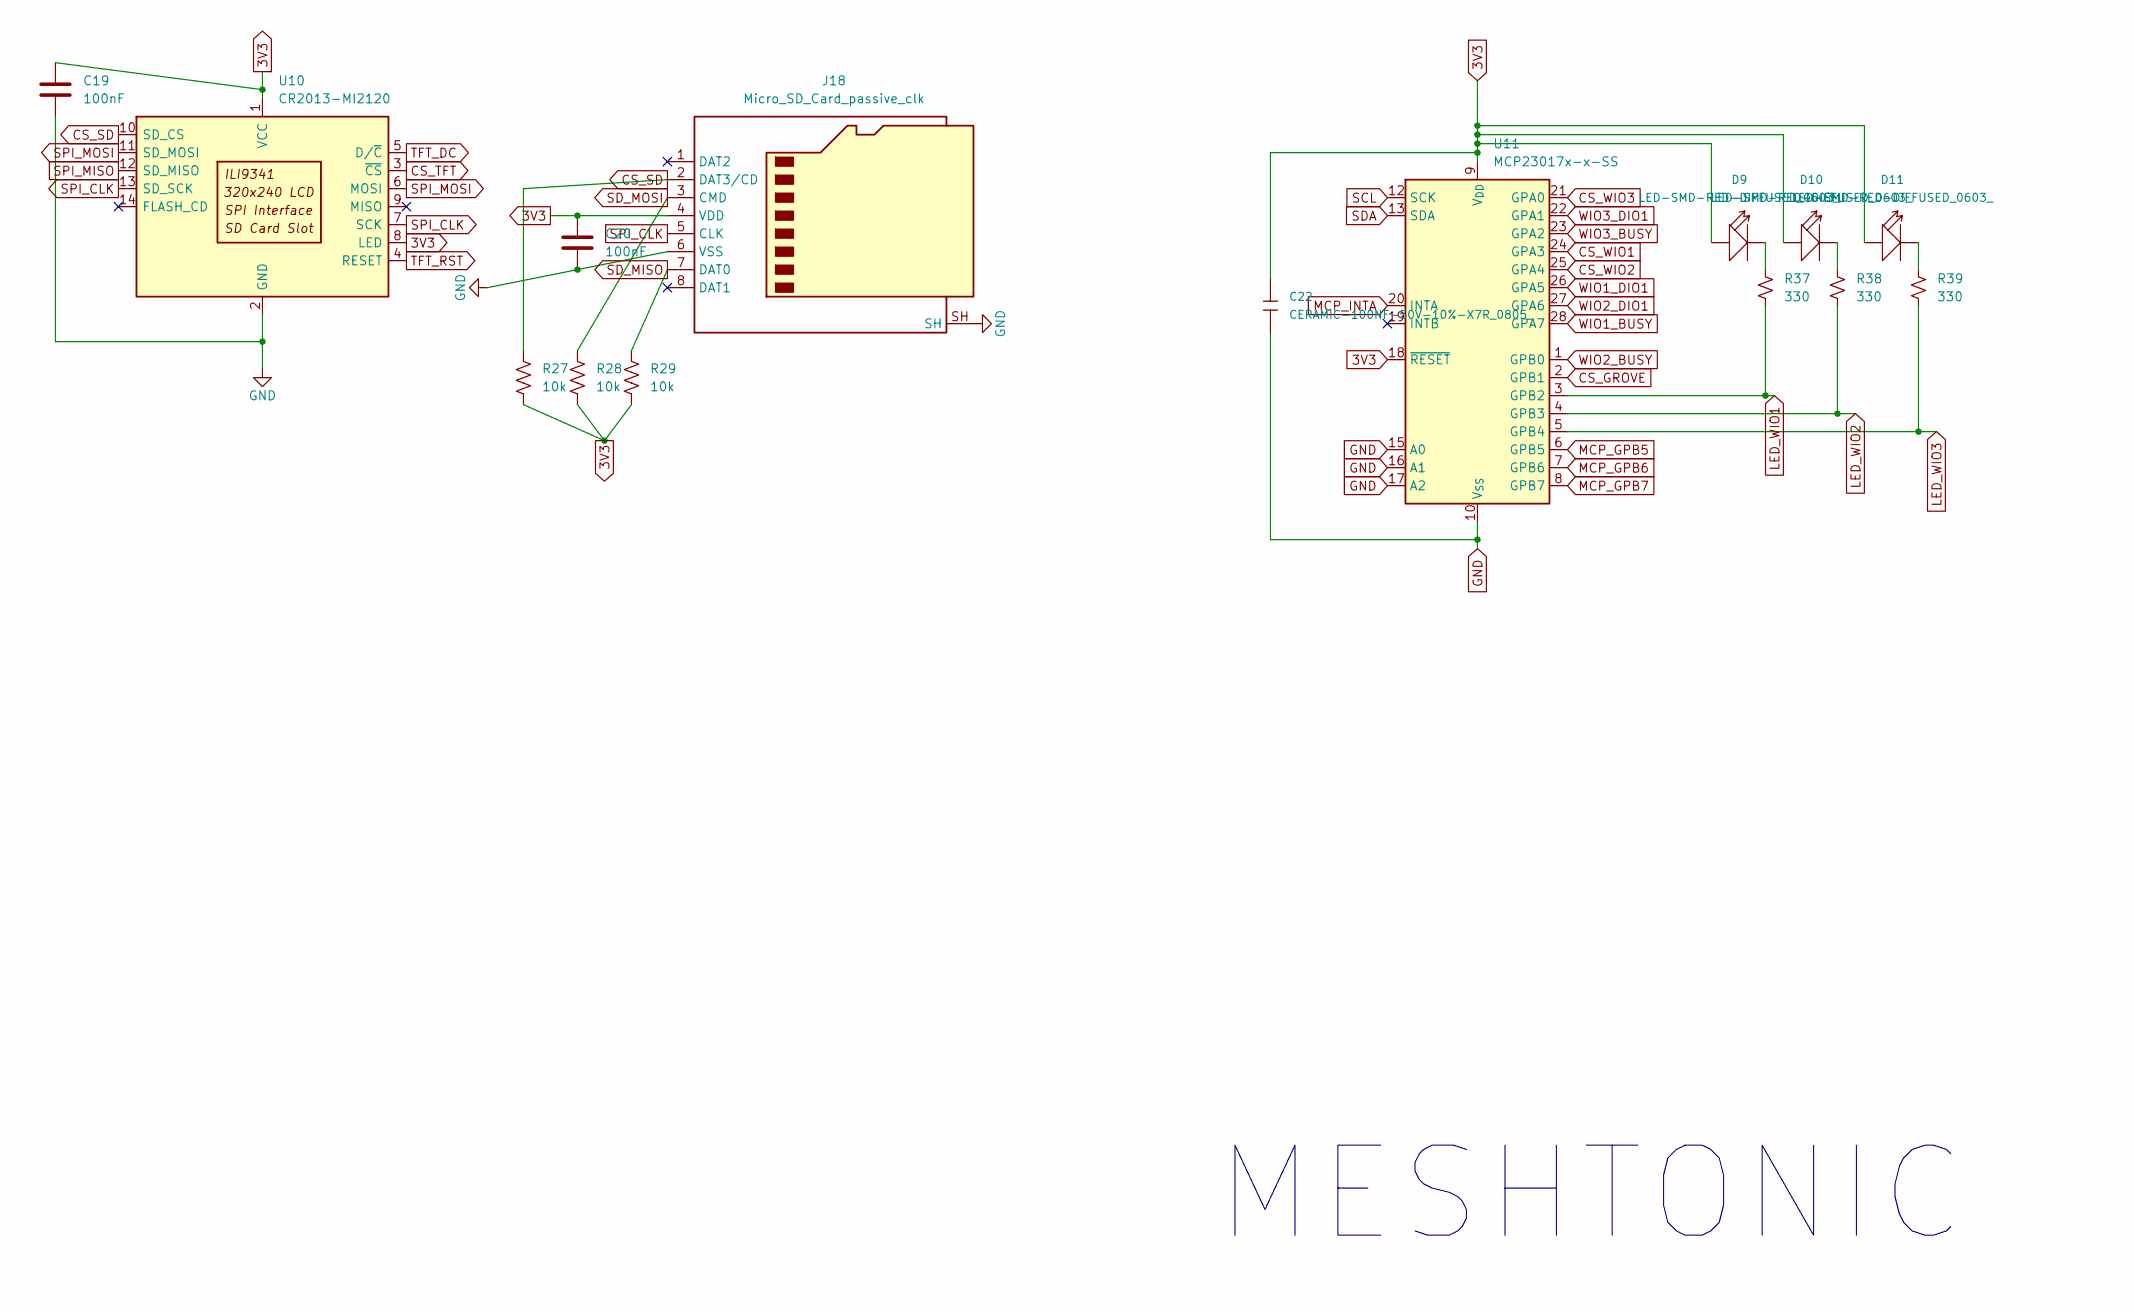
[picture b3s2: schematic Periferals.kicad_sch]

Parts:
C19, C20: 100nF; C_0603_1608Metric
C22: CERAMIC-100NF-50V-10%-X7R_0805_; MPN CC0805KRX7R9BB104
D9, D10, D11: LED-SMD-RED-DIFFUSED_0603_; LED_0603_1608Metric; MPN 19-217-R6C-AL1M2VY-3T
J18: Micro_SD_Card_passive_clk; MICRO-SD9+4P-SMD-16.1X14.5X1.85MM
R27, R28, R29: 10k; R_0603_1608Metric
R37, R38, R39: 330; R_0603_1608Metric
U10: CR2013-MI2120
U11: MCP23017x-x-SS; SSOP-28_5.3x10.2mm_P0.65mm

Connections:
3V3: C19.1, C20.1, C22.2, D9.1 (+), D10.1 (+), D11.1 (+), J18.4 (VDD), R27.2, R28.2, R29.2, U10.1 (VCC), U10.8 (LED), U11.9 (V_{DD}), U11.18 (~RESET); also elsewhere on the board
CS_GROVE: U11.2 (GPB1)
CS_SD: J18.2 (DAT3/CD), R27.1, U10.10 (SD_CS); also elsewhere on the board
CS_TFT: U10.3 (~CS); also elsewhere on the board
CS_WIO1: U11.24 (GPA3); also elsewhere on the board
CS_WIO2: U11.25 (GPA4); also elsewhere on the board
CS_WIO3: U11.21 (GPA0); also elsewhere on the board
GND: C19.2, C20.2, C22.1, J18.6 (VSS), J18.SH, U10.2 (GND), U11.10 (V_{SS}), U11.15 (A0), U11.16 (A1), U11.17 (A2); also elsewhere on the board
LED_WIO1: R37.1, U11.3 (GPB2)
LED_WIO2: R38.1, U11.4 (GPB3)
LED_WIO3: R39.1, U11.5 (GPB4)
MCP_GPB5: U11.6 (GPB5); also elsewhere on the board
MCP_GPB6: U11.7 (GPB6); also elsewhere on the board
MCP_GPB7: U11.8 (GPB7); also elsewhere on the board
MCP_INTA: U11.20 (INTA); also elsewhere on the board
unnamed: D9.2 (-), R37.2
unnamed: D10.2 (-), R38.2
unnamed: D11.2 (-), R39.2
SCL: U11.12 (SCK); also elsewhere on the board
SDA: U11.13 (SDA); also elsewhere on the board
SD_MISO: J18.7 (DAT0), R29.1
SD_MOSI: J18.3 (CMD), R28.1
SPI_CLK: J18.5 (CLK), U10.7 (SCK), U10.13 (SD_SCK); also elsewhere on the board
SPI_MISO: U10.12 (SD_MISO); also elsewhere on the board
SPI_MOSI: U10.6 (MOSI), U10.11 (SD_MOSI); also elsewhere on the board
TFT_DC: U10.5 (D/~C); also elsewhere on the board
TFT_RST: U10.4 (RESET); also elsewhere on the board
WIO1_BUSY: U11.28 (GPA7); also elsewhere on the board
WIO1_DIO1: U11.26 (GPA5); also elsewhere on the board
WIO2_BUSY: U11.1 (GPB0); also elsewhere on the board
WIO2_DIO1: U11.27 (GPA6); also elsewhere on the board
WIO3_BUSY: U11.23 (GPA2); also elsewhere on the board
WIO3_DIO1: U11.22 (GPA1); also elsewhere on the board

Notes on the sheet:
MESHTONIC

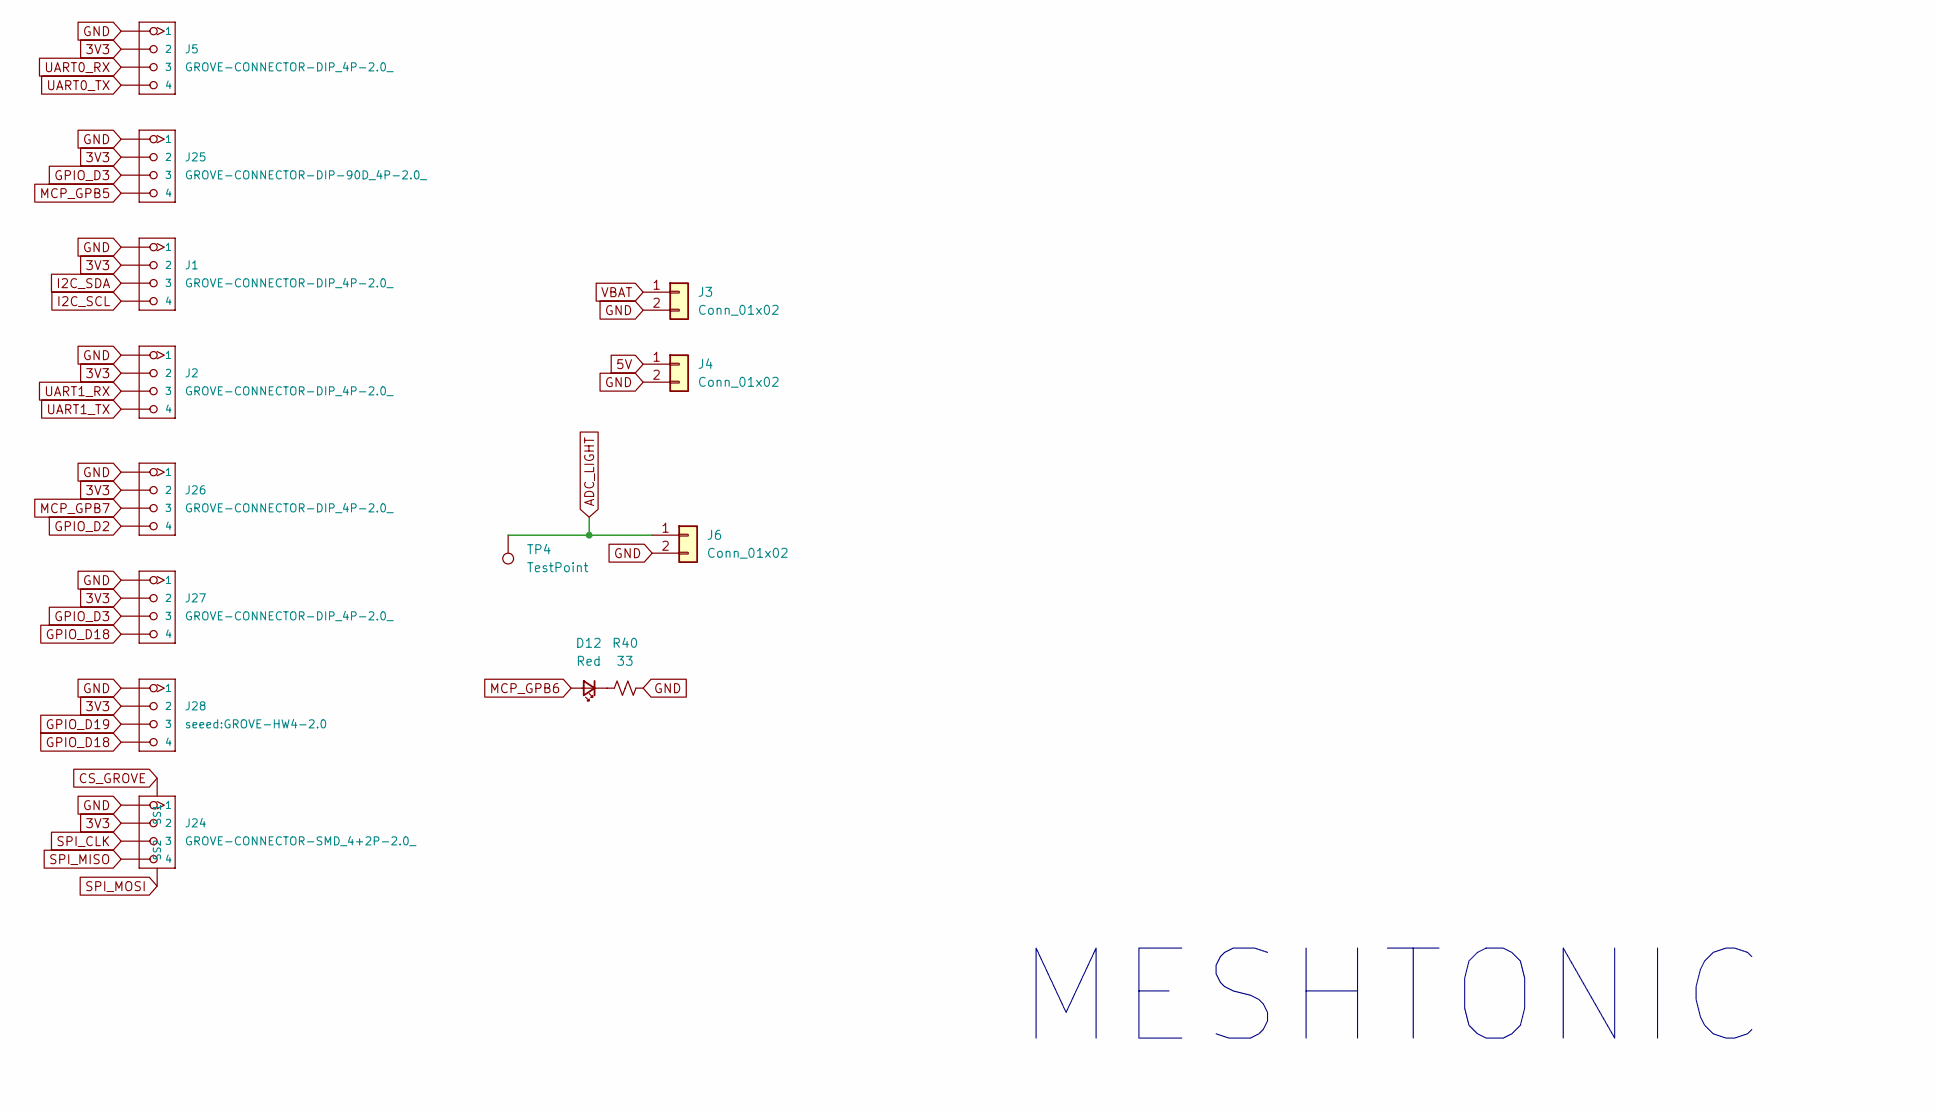
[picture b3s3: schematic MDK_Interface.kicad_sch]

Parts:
D12: Red; LED_0402_1005Metric_Red
J1, J2, J5, J26, J27: GROVE-CONNECTOR-DIP_4P-2.0_; GROVE-HW4-2.0
J3, J4, J6: Conn_01x02; 1x02_P2.54mm
J24: GROVE-CONNECTOR-SMD_4+2P-2.0_; GROVE-HW4-SMD-2.0
J25: GROVE-CONNECTOR-DIP-90D_4P-2.0_; GROVE-HW4-2.0-90D
J28: seeed:GROVE-HW4-2.0; GROVE-HW4-2.0
R40: 33; R_0402_1005Metric
TP4: TestPoint

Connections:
3V3: J1.2, J2.2, J5.2, J24.2, J25.2, J26.2, J27.2, J28.2; also elsewhere on the board
5V: J4.1
ADC_LIGHT: J6.1, TP4.1; also elsewhere on the board
GND: J1.1, J2.1, J3.2, J4.2, J5.1, J6.2, J24.1, J25.1, J26.1, J27.1, J28.1, R40.2; also elsewhere on the board
GPIO_D2: J26.4; also elsewhere on the board
GPIO_D3: J25.3, J27.3; also elsewhere on the board
GPIO_D18: J27.4, J28.4; also elsewhere on the board
GPIO_D19: J28.3; also elsewhere on the board
I2C_SCL: J1.4; also elsewhere on the board
I2C_SDA: J1.3; also elsewhere on the board
MCP_GPB5: J25.4; also elsewhere on the board
MCP_GPB6: D12.2 (A); also elsewhere on the board
MCP_GPB7: J26.3; also elsewhere on the board
unnamed: D12.1 (K), R40.1
SPI_CLK: J24.3; also elsewhere on the board
SPI_MISO: J24.4; also elsewhere on the board
UART0_RX: J5.3; also elsewhere on the board
UART0_TX: J5.4; also elsewhere on the board
UART1_RX: J2.3; also elsewhere on the board
UART1_TX: J2.4; also elsewhere on the board
VBAT: J3.1; also elsewhere on the board

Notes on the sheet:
MESHTONIC
